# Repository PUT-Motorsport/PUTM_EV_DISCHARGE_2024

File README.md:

# Specs

Discharge resistors: 3kR 100W  
Capacitors: 300uF  
Relay: https://www.cynergy3.com/sites/default/files/cynergy3-d-v3.pdf  
Connectors: 3 pin deutsch d369

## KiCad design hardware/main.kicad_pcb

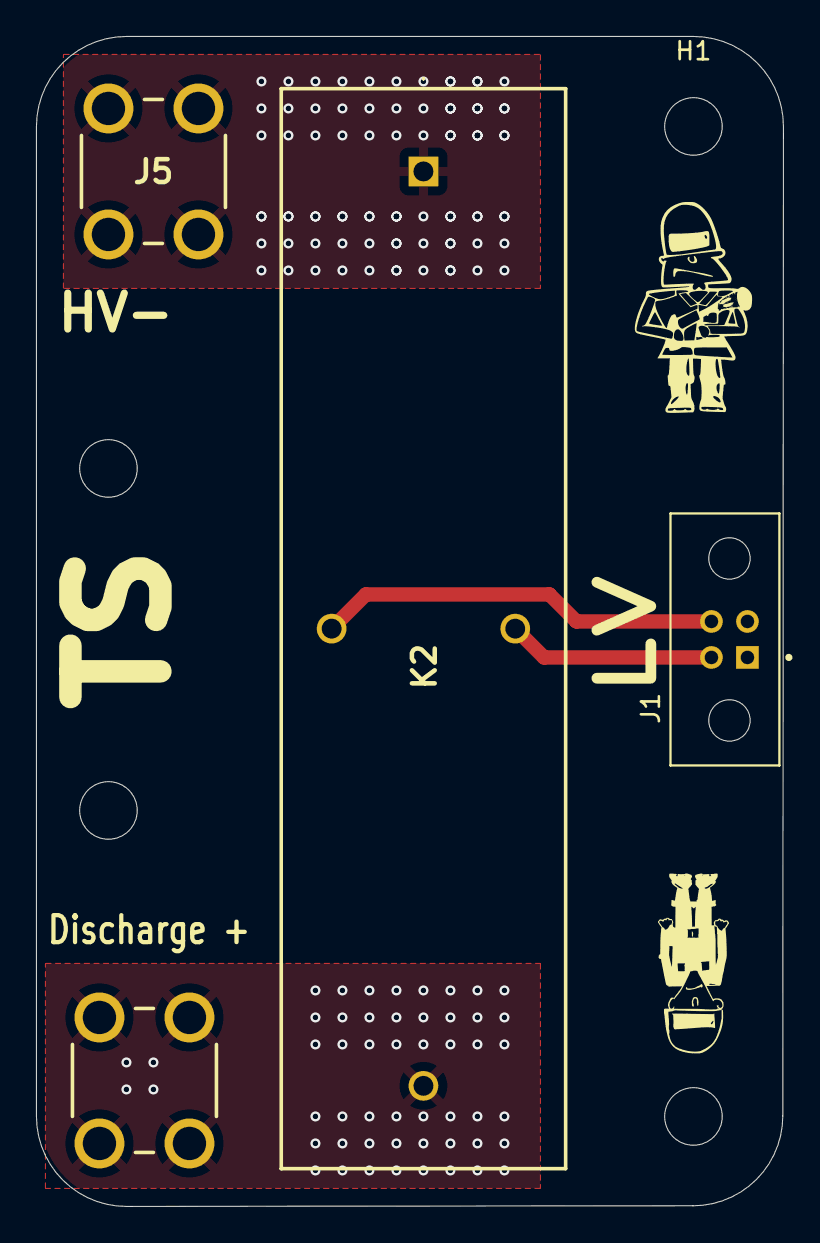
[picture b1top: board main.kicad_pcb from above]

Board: 2 copper layers, 41.5 x 65.0 mm, 9 parts (0 on the bottom side), 4 nets.

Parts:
H1, H2, H3, H3#2, H4: MountingHole; MountingHole_3.2mm_M3
J1: Conn_01x04; HARWIN_M80-5100442
J4, J5: ScrewTerminal; 7696
K2: ADW11; DBR72410

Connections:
/HV+_dIscharge_resistors: J4.1, K2.2
GND: J1.3, K2.4
HV-: J5.1, K2.1
SD+: J1.2, K2.3

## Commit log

2024-02-19 -m "project added"
2024-02-20 Full Schematic
2024-02-27 add connectors and change through hole for HV
2024-02-27 changed Resistors and HV Cables
2024-02-28 Still have to take the measurements
2024-03-03 Added calculations
2024-03-07 changed resistors
2024-03-08 updated layout with connections
2024-03-08 added logo
2024-03-11 updated schematic with measures
2024-03-15 Fabrication Toolkit files added
2024-03-19 added options
2024-03-20 Changed resistors to 3x 2k 50W
2024-03-20 updated calculations
2024-04-30 fixed error with the connector
2024-06-18 Changing the J2 connector
    Adapting the connector to the existing harness for PM 09
2025-05-05 Zmniejszona
2025-05-06 Changed the creepage distance between HV and LV, changed thermal refielf for TSMP resistors
2025-05-22 Usunięto rezystory discharge z pcb, zmniejszono płytkę
2025-05-24 dodano folder fab, wersja 2.0 gotowa
